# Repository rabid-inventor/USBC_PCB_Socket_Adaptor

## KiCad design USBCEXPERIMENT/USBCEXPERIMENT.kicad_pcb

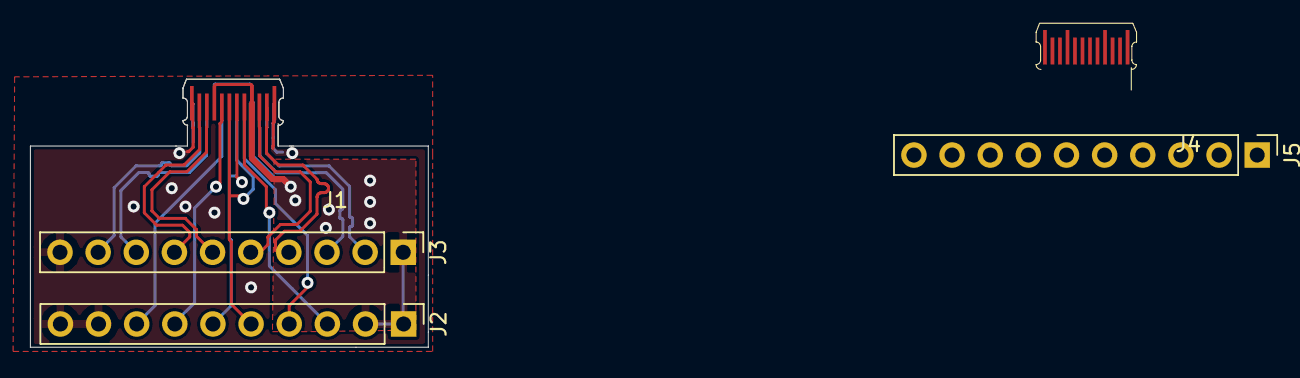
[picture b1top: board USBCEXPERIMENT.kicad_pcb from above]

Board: 2 copper layers, 26.5 x 17.9 mm, 5 parts (0 on the bottom side), 16 nets.

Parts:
J1, J4: USB_C_Receptacle; usb-c-pcb
J2, J3, J5: Conn_01x10_Male; PinHeader_1x10_P2.54mm_Vertical

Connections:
/CC1: J1.A5, J2.3, J4.A5, J5.3
/CC2: J1.B5, J2.8, J4.B5, J5.8
/RX1+: J1.B11, J3.2
/RX1-: J1.B10, J3.3
/RX2+: J1.A11, J3.7
/RX2-: J1.A10, J3.6
/SBUS1: J1.A8, J2.7, J4.A8, J5.7
/SBUS2: J1.B8, J2.4, J4.B8, J5.4
/TX1+: J1.A2, J3.4
/TX1-: J1.A3, J3.5
/TX2+: J1.B2, J3.9
/TX2-: J1.B3, J3.8
/USBD+: J1.A6, J1.B6, J2.6, J4.A6, J4.B6, J5.6
/USBD-: J1.A7, J1.B7, J2.5, J4.A7, J4.B7, J5.5
GND: J1.A1, J1.A12, J1.B1, J1.B12, J2.9, J2.10, J3.10, J4.A1, J4.A12, J4.B1, J4.B12, J5.9, J5.10
VBUS: J1.A4, J1.A9, J1.B4, J1.B9, J2.1, J2.2, J3.1, J4.A4, J4.A9, J4.B4, J4.B9, J5.1, J5.2

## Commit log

2020-07-23 figuring how to do the SS traces
2020-07-23 started to add a simple version to the PCB
2020-07-27 more work in progress
